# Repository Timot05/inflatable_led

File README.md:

# A portable light printed using Rapid Liquid Printing

## Specs

- 2700K
- About 400 lumens
- Dimmable
- Rechargeable
- Flashes when battery low

## Implementation

- Micro: RP2040
- LED Driver: TPS61165
- LED: OSRAM GW JTLPS1.EM-KKLL-XX58-1
- Batteries: TBD
- Battery charger: TBD

## TODOs for V1 order:

- Check order of LEDs
- Check the caps footprint
- C15, C16 are wrong size
- Remove todo from schematic

## TODOs for v2:

- [x] Add charging status to micro
- [x] fix the led circuit switching
- [x] enable low power mode with reset switch (no long press. How did we switch all circuits on mopi?)
- [x] Remove the cap on qspi_ss
- [x] DNP for the 3.3V led
- [x] Add a buck boost instead of ldo -> Remain with LDO but remove shotky diode (need to add it in case?)
- [x] Check the bat sense feature - probs ok
- [x] White circuit for reflection - will do
- [ ] Add gnd, vref, 3.3V to the debug port
- [x] Add the 10k resistor to the TS pin on the charger -> changed charger and fixed TS
- [x] Switch to ULDO
- [x] Change the battery holder -> changed to double battery holder

Nice to have:

- i2c connected charger
- Protrude the button more
- Nice feeling button

## TODOs for V3

- [ ] add a label for +/- battery
- [ ] remove the pullup on the on/off bt
- [ ] add a blinky led

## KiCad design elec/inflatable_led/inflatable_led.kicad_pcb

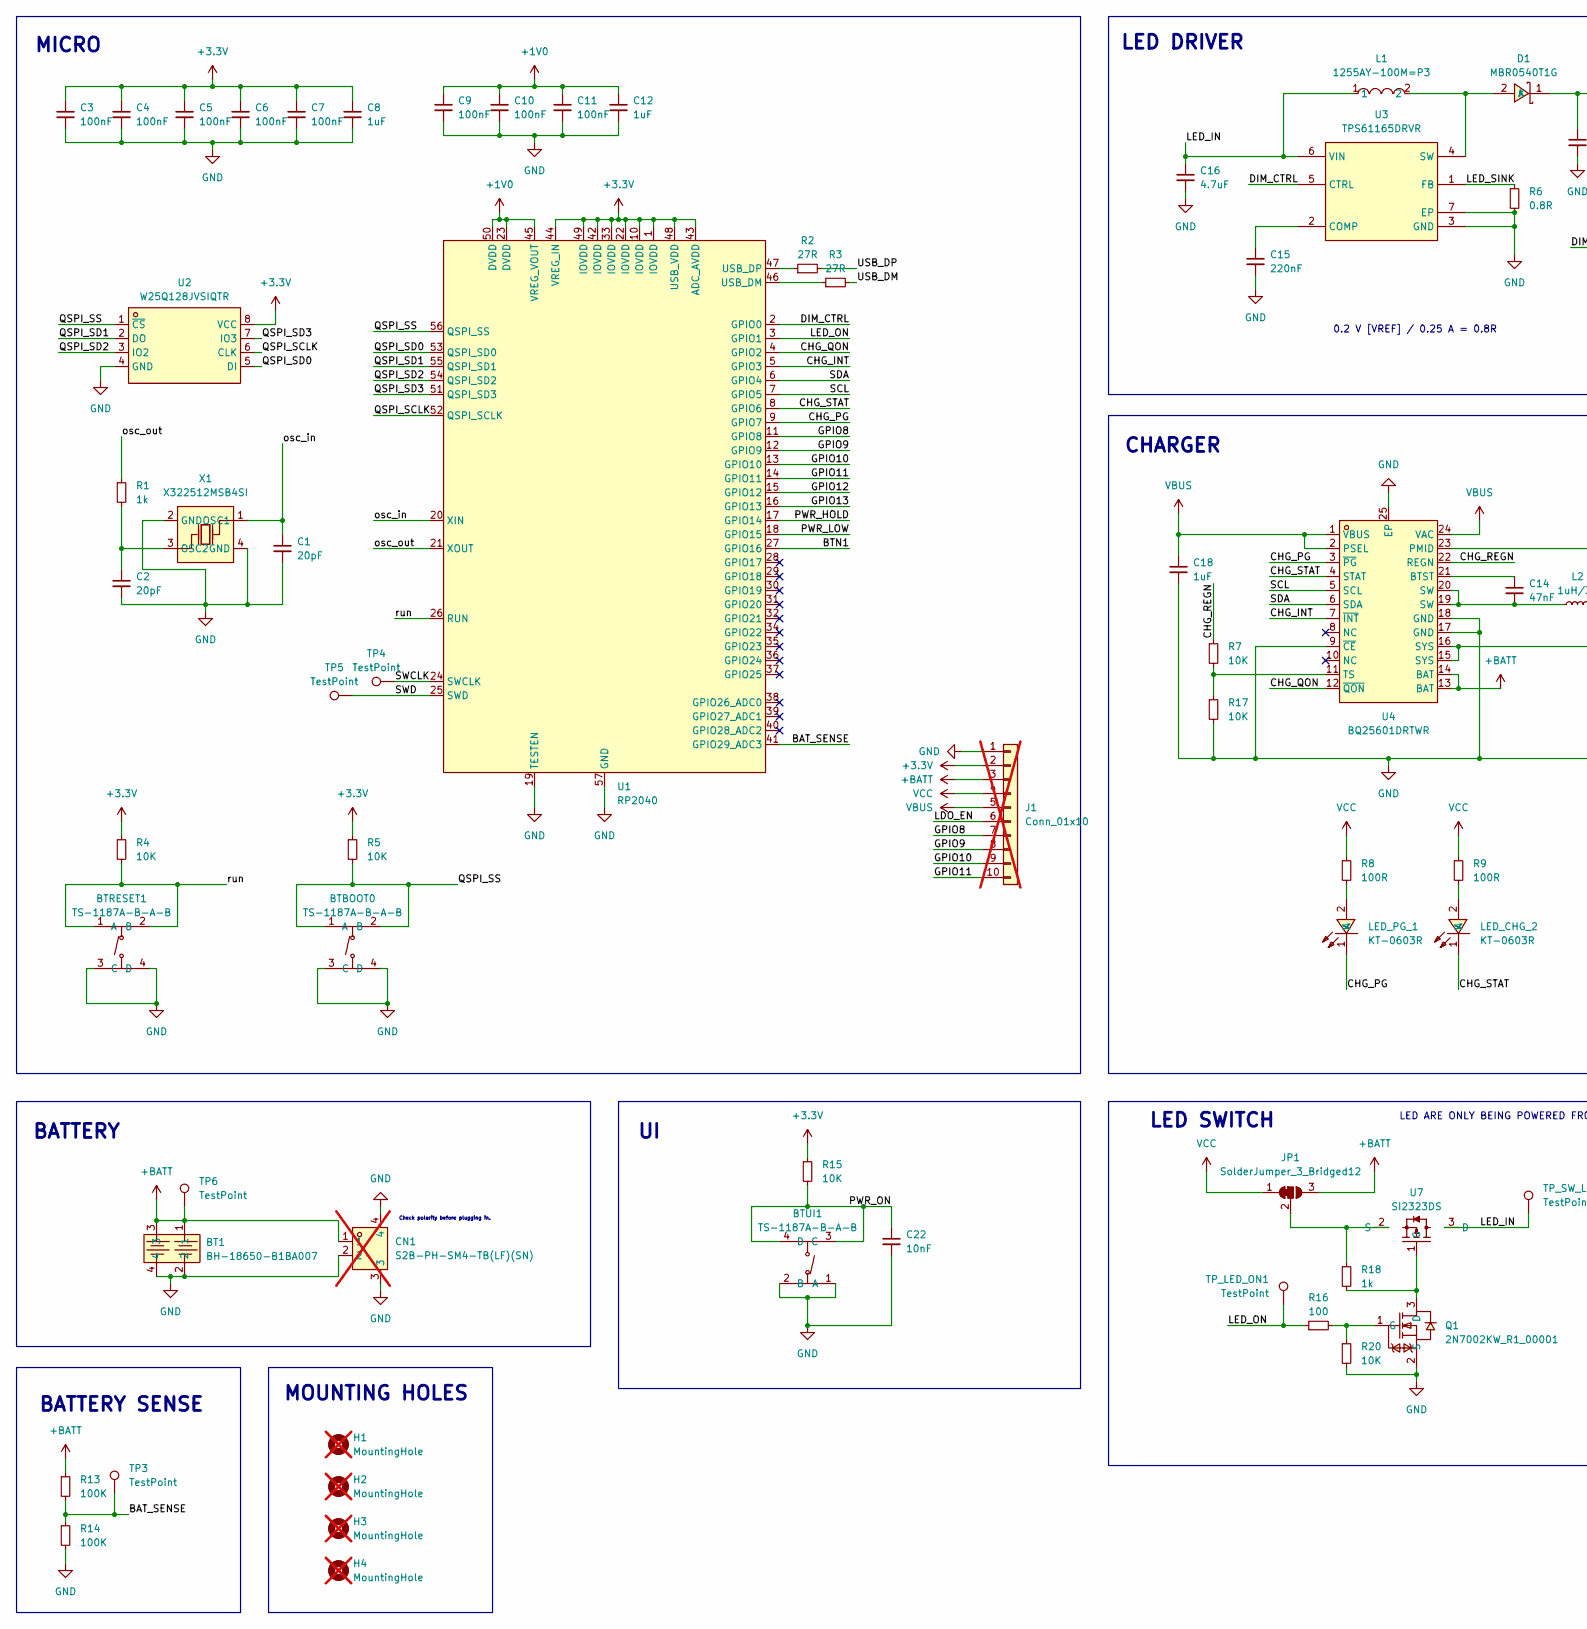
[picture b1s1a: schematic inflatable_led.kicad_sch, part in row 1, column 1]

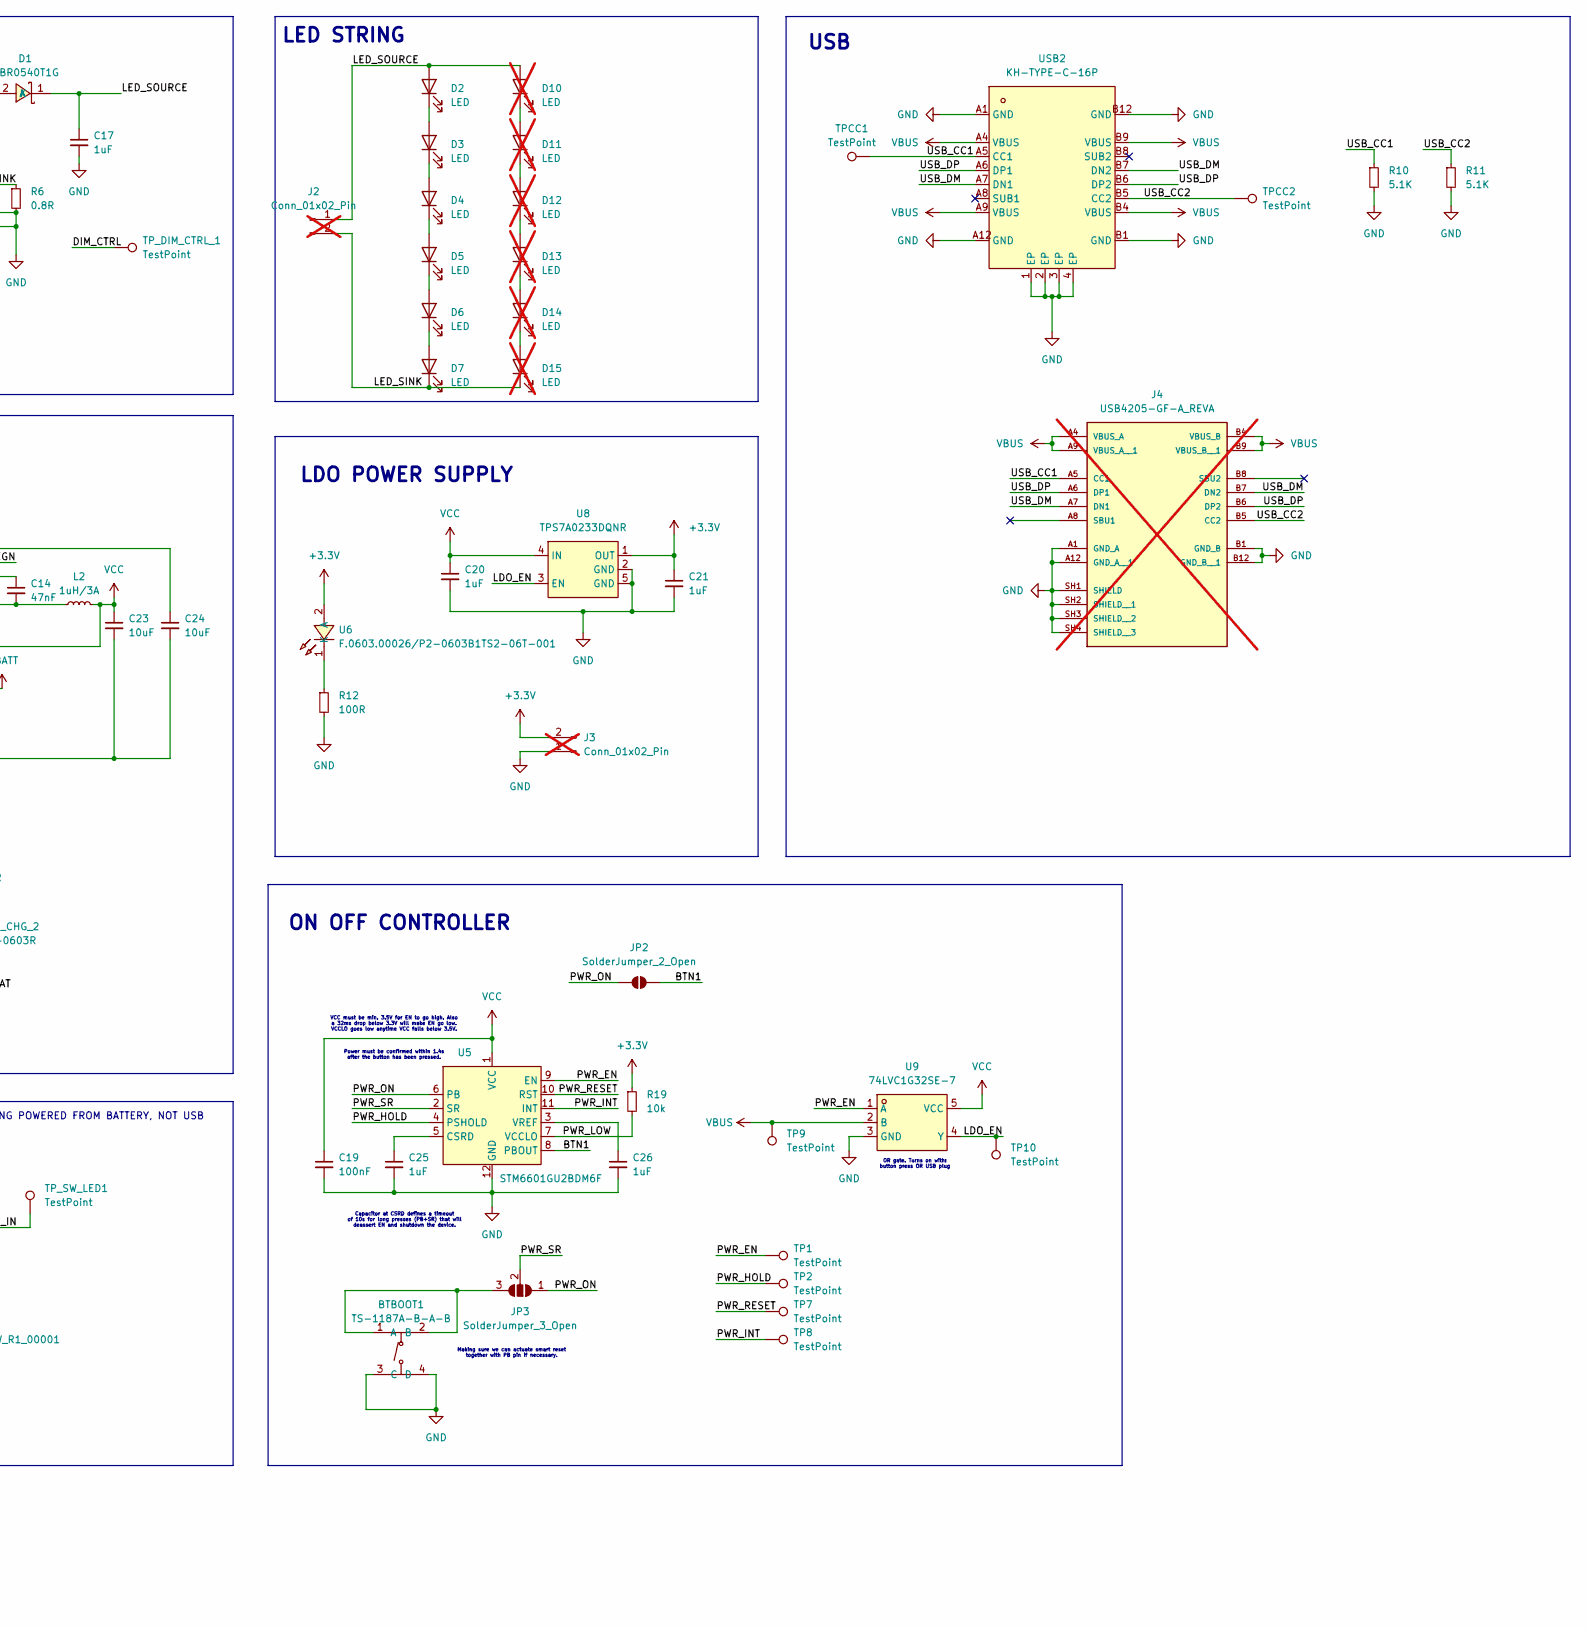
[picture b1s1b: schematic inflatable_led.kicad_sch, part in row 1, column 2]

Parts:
BT1: BH-18650-B1BA007; BAT-SMD_BH-18650-B1BA007; LCSC Part C6937126
BTBOOT0, BTBOOT1: TS-1187A-B-A-B; SW-SMD_4P-L5.1-W5.1-P3.70-LS6.5-TL-2; LCSC Part C318884
BTRESET1: TS-1187A-B-A-B; SW-SMD_4P-L5.1-W5.1-P3.70-LS6.5-TL-2; LCSC Part C318884
BTUI1: TS-1187A-B-A-B; SW-SMD_4P-L5.1-W5.1-P3.70-LS6.5-TL-2; LCSC Part C318884
C1, C2: 20pF; C_0402_1005Metric; LCSC Part C1554
C3, C4, C5, C6, C7, C9, C10, C11: 100nF; C_0402_1005Metric; LCSC Part C1525
C8, C12, C17, C18, C20, C21: 1uF; C_0805_2012Metric; LCSC Part C28323
C14: 47nF; C_0402_1005Metric; Digikey 311-1801-1-ND
C15: 220nF; C_0402_1005Metric; LCSC Part C16772
C16: 4.7uF; C_0402_1005Metric; LCSC Part C23733
C19: 100nF; C_0402_1005Metric; Digikey 311-1776-1-ND
C22: 10nF; C_0402_1005Metric; LCSC Part C15195
C23, C24: 10uF; C_0805_2012Metric; LCSC Part C15850
C25, C26: 1uF; C_0805_2012Metric; Digikey 311-1444-1-ND
CN1: S2B-PH-SM4-TB(LF)(SN); CONN-SMD_P2.00_S2B-PH-SM4-TB-LF-SN; LCSC Part C295747; not fitted
D1: MBR0540T1G; SOD-123_L2.8-W1.8-LS3.7-RD; LCSC Part C109213
D2, D3, D4, D5, D6, D7: LED; GW JTLPS1EM; LCSC Part C5220764
D10: LED; GW JTLPS1EM; LCSC Part C5220764; not fitted
D11, D12, D13, D14, D15: LED; GW JTLPS1EM; not fitted
H1, H2, H3, H4: MountingHole; MountingHole_3.2mm_M3_Pad_Via; not fitted
J1: Conn_01x10; PinHeader_1x10_P1.00mm_Vertical; not fitted
J2, J3: Conn_01x02_Pin; PinHeader_1x02_P2.54mm_Vertical; not fitted
J4: USB4205-GF-A_REVA; GCT_USB4205-GF-A_REVA; PARTREV A; not fitted
JP1: SolderJumper_3_Bridged12; SolderJumper-3_P1.3mm_Bridged12_RoundedPad1.0x1.5mm
JP2: SolderJumper_2_Open; SolderJumper-2_P1.3mm_Open_TrianglePad1.0x1.5mm
JP3: SolderJumper_3_Open; SolderJumper-3_P2.0mm_Open_TrianglePad1.0x1.5mm
L1: 1255AY-100M=P3; IND-SMD_L6.0-W6.0; LCSC Part C160950
L2: 1uH/3A; L_1008_2520Metric; Digikey 1276-6929-1-ND
LED_CHG_2: KT-0603R; LED0603-RD; LCSC Part C2286
LED_PG_1: KT-0603R; LED0603-RD; LCSC Part C2286
Q1: 2N7002KW_R1_00001; SOT-323-3_L2.0-W1.3-P1.30-LS2.1-BR; LCSC Part C313495
R1, R18: 1k; R_0402_1005Metric; LCSC Part C11702
R2, R3: 27R; R_0402_1005Metric; LCSC Part C25100
R4, R5, R7, R15, R17, R20: 10K; R_0402_1005Metric; LCSC Part C25744
R6: 0.8R; R_0805_2012Metric_Pad1.20x1.40mm_HandSolder; LCSC Part C175720
R8, R9, R12: 100R; R_0402_1005Metric; LCSC Part C25076
R10, R11: 5.1K; R_0402_1005Metric; LCSC Part C25905
R13, R14: 100K; R_0402_1005Metric; LCSC Part C25741
R16: 100; R_0402_1005Metric; LCSC Part C25076
R19: 10k; R_0402_1005Metric; Digikey 311-10.0KHRCT-ND
TP1, TP2, TP7, TP8, TP9, TP10: TestPoint; TestPoint_Pad_D1.0mm
TP3, TP4, TP5, TP6: TestPoint; TestPoint_Pad_D1.5mm
TPCC1, TPCC2: TestPoint; TestPoint_Pad_D1.5mm
TP_DIM_CTRL_1: TestPoint; TestPoint_Pad_D1.5mm
TP_LED_ON1: TestPoint; TestPoint_Pad_D1.5mm
TP_SW_LED1: TestPoint; TestPoint_Pad_D1.5mm
U1: RP2040; LQFN-56_L7.0-W7.0-P0.4-EP; LCSC Part C2040
U2: W25Q128JVSIQTR; SOIC-8_L5.3-W5.3-P1.27-LS8.0-BL; LCSC Part C97521
U3: TPS61165DRVR; WSON-6_L2.0-W2.0-P0.65-TL-EP; LCSC Part C122568
U4: BQ25601DRTWR; WQFN-24_L4.0-W4.0-P0.50-TL-EP2.7; LCSC Part C2859691
U5: STM6601GU2BDM6F; TDFN-12_2x3mm_P0.5mm; Digikey 497-14857-1-ND
U6: F.0603.00026/P2-0603B1TS2-06T-001; LED0603-RD; LCSC Part C7496819
U7: SI2323DS; SOT-23-3_L2.9-W1.3-P1.90-LS2.4-BR; LCSC Part C5182044
U8: TPS7A0233DQNR; X2SON-4_L1.0-W1.0-P0.65-TL-EP; LCSC Part C5220177
U9: 74LVC1G32SE-7; SOT-353_L2.0-W1.2-P0.65-LS2.1-BL; LCSC Part C460530
USB2: KH-TYPE-C-16P; USB-C-SMD_KH-TYPE-C-16P; LCSC Part C709357
X1: X322512MSB4SI; OSC-SMD_4P-L3.2-W2.5-BL; LCSC Part C9002

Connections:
+1V0: C9.1, C10.1, C11.1, C12.1, U1.23 (DVDD), U1.45 (VREG_VOUT), U1.50 (DVDD)
+3.3V: C3.1, C4.1, C5.1, C6.1, C7.1, C8.1, C21.1, J1.2, J3.2, R4.1, R5.1, R15.1, R19.1, U1.1 (IOVDD), U1.10 (IOVDD), U1.22 (IOVDD), U1.33 (IOVDD), U1.42 (IOVDD), U1.43 (ADC_AVDD), U1.44 (VREG_IN), U1.48 (USB_VDD), U1.49 (IOVDD), U2.8 (VCC), U6.2 (A), U8.1 (OUT)
+BATT: BT1.1, BT1.3, CN1.1, J1.3, JP1.3 (B), R13.1, TP6.1, U4.13 (BAT), U4.14 (BAT)
/BAT_SENSE: R13.2, R14.1, TP3.1, U1.41 (GPIO29_ADC3)
/BTN1: JP2.2 (B), U1.27 (GPIO16), U5.8 (PBOUT)
/CHG_INT: U1.5 (GPIO3), U4.7 (~INT)
/CHG_PG: LED_PG_1.1 (K), U1.9 (GPIO7), U4.3 (~PG)
/CHG_QON: U1.4 (GPIO2), U4.12 (~QON)
/CHG_REGN: R7.1, U4.22 (REGN)
/CHG_STAT: LED_CHG_2.1 (K), U1.8 (GPIO6), U4.4 (STAT)
/DIM_CTRL: TP_DIM_CTRL_1.1, U1.2 (GPIO0), U3.5 (CTRL)
/GPIO8: J1.7, U1.11 (GPIO8)
/GPIO9: J1.8, U1.12 (GPIO9)
/GPIO10: J1.9, U1.13 (GPIO10)
/GPIO11: J1.10, U1.14 (GPIO11)
/GPIO12: U1.15 (GPIO12)
/GPIO13: U1.16 (GPIO13)
/LDO_EN: J1.6, TP10.1, U8.3 (EN), U9.4 (Y)
/LED_IN: C16.1, L1.1, TP_SW_LED1.1, U3.6 (VIN), U7.3 (D)
/LED_ON: R16.1, TP_LED_ON1.1, U1.3 (GPIO1)
/LED_SINK: D7.1 (K), D15.1 (K), J2.2, R6.1, U3.1 (FB)
/LED_SOURCE: C17.1, D1.1 (K), D2.2 (A), D10.2 (A), J2.1
/PWR_EN: TP1.1, U5.9 (EN), U9.1 (A)
/PWR_HOLD: TP2.1, U1.17 (GPIO14), U5.4 (PSHOLD)
/PWR_INT: TP8.1, U5.11 (INT)
/PWR_LOW: R19.2, U1.18 (GPIO15), U5.7 (VCCLO)
/PWR_ON: BTUI1.3 (C), BTUI1.4 (D), C22.1, JP2.1 (A), JP3.1 (A), R15.2, U5.6 (PB)
/PWR_RESET: TP7.1, U5.10 (RST)
/PWR_SR: JP3.2 (C), U5.2 (SR)
/QSPI_SCLK: U1.52 (QSPI_SCLK), U2.6 (CLK)
/QSPI_SD0: U1.53 (QSPI_SD0), U2.5 (DI)
/QSPI_SD1: U1.55 (QSPI_SD1), U2.2 (DO)
/QSPI_SD2: U1.54 (QSPI_SD2), U2.3 (IO2)
/QSPI_SD3: U1.51 (QSPI_SD3), U2.7 (IO3)
/QSPI_SS: BTBOOT0.1 (A), BTBOOT0.2 (B), R5.2, U1.56 (QSPI_SS), U2.1 (~CS)
/SCL: U1.7 (GPIO5), U4.5 (SCL)
/SDA: U1.6 (GPIO4), U4.6 (SDA)
/SWCLK: TP4.1, U1.24 (SWCLK)
/SWD: TP5.1, U1.25 (SWD)
/USB_CC1: J4.A5 (CC1), R10.1, TPCC1.1, USB2.A5 (CC1)
/USB_CC2: J4.B5 (CC2), R11.1, TPCC2.1, USB2.B5 (CC2)
/USB_DM: J4.A7 (DN1), J4.B7 (DN2), R3.2, USB2.A7 (DN1), USB2.B7 (DN2)
/USB_DP: J4.A6 (DP1), J4.B6 (DP2), R2.2, USB2.A6 (DP1), USB2.B6 (DP2)
/osc_in: C1.1, U1.20 (XIN), X1.1 (OSC1)
/osc_out: R1.1, U1.21 (XOUT)
/run: BTRESET1.1 (A), BTRESET1.2 (B), R4.2, U1.26 (RUN)
GND: BT1.2, BT1.4, BTBOOT0.3 (C), BTBOOT0.4 (D), BTBOOT1.3 (C), BTBOOT1.4 (D), BTRESET1.3 (C), BTRESET1.4 (D), BTUI1.1 (A), BTUI1.2 (B), C1.2, C2.2, C3.2, C4.2, C5.2, C6.2, C7.2, C8.2, C9.2, C10.2, C11.2, C12.2, C15.2, C16.2, C17.2, C18.2, C19.2, C20.2, C21.2, C22.2, C23.2, C24.2, C25.2, C26.2, CN1.2, CN1.3, CN1.4, J1.1, J3.1, J4.A1 (GND_A), J4.A12 (GND_A__1), J4.B1 (GND_B), J4.B12 (GND_B__1), J4.SH1 (SHIELD), J4.SH2 (SHIELD__1), J4.SH3 (SHIELD__2), J4.SH4 (SHIELD__3), Q1.2 (S), R6.2, R10.2, R11.2, R12.2, R14.2, R17.2, R20.2, U1.19 (TESTEN), U1.57 (GND), U2.4 (GND), U3.3 (GND), U3.7 (EP), U4.9 (~CE), U4.17 (GND), U4.18 (GND), U4.25 (EP), U5.12 (GND), U8.2 (GND), U8.5 (GND), U9.3 (GND), USB2.1 (EP), USB2.2 (EP), USB2.3 (EP), USB2.4 (EP), USB2.A1 (GND), USB2.A12 (GND), USB2.B1 (GND), USB2.B12 (GND), X1.2 (GND), X1.4 (GND)
unnamed: BTBOOT1.1 (A), BTBOOT1.2 (B), JP3.3 (B)
unnamed: C14.2, L2.1, U4.19 (SW), U4.20 (SW)
unnamed: D1.2 (A), L1.2, U3.4 (SW)
unnamed: D2.1 (K), D3.2 (A)
unnamed: D3.1 (K), D4.2 (A)
unnamed: D4.1 (K), D5.2 (A)
unnamed: D5.1 (K), D6.2 (A)
unnamed: D6.1 (K), D7.2 (A)
unnamed: D10.1 (K), D11.2 (A)
unnamed: D11.1 (K), D12.2 (A)
unnamed: D12.1 (K), D13.2 (A)
unnamed: D13.1 (K), D14.2 (A)
unnamed: D14.1 (K), D15.2 (A)
unnamed: JP1.2 (C), R18.1, U7.2 (S)
unnamed: LED_CHG_2.2 (A), R9.2
unnamed: LED_PG_1.2 (A), R8.2
unnamed: Q1.3 (D), R18.2, U7.1 (G)
unnamed: Q1.1 (G), R16.2, R20.1
unnamed: R3.1, U1.46 (USB_DM)
unnamed: R2.1, U1.47 (USB_DP)
unnamed: C15.1, U3.2 (COMP)
unnamed: C14.1, U4.21 (BTST)
unnamed: C24.1, U4.23 (PMID)
unnamed: R7.2, R17.1, U4.11 (TS)
unnamed: C25.1, U5.5 (CSRD)
unnamed: C26.1, U5.3 (VREF)
unnamed: R12.1, U6.1 (K)
unnamed: C2.1, R1.2, X1.3 (OSC2)
VBUS: C18.1, J1.5, J4.A4 (VBUS_A), J4.A9 (VBUS_A__1), J4.B4 (VBUS_B), J4.B9 (VBUS_B__1), TP9.1, U4.1 (VBUS), U4.2 (PSEL), U4.24 (VAC), U9.2 (B), USB2.A4 (VBUS), USB2.A9 (VBUS), USB2.B4 (VBUS), USB2.B9 (VBUS)
VCC: C19.1, C20.1, C23.1, J1.4, JP1.1 (A), L2.2, R8.1, R9.1, U4.15 (SYS), U4.16 (SYS), U5.1 (VCC), U8.4 (IN), U9.5 (VCC)

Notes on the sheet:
OR gate. Turns on with: button press OR USB plug
VCC must be min. 3.5V for EN to go high. Also a 32ms drop below 3.3V will make EN go low. VCCLO goes low anytime VCC falls below 3.5V. Power must be confirmed within 1.4s after the button has been pressed.
Capacitor at CSRD defines a timeout of 10s for long presses (PB+SR) that will deassert EN and shutdown the device.
LED ARE ONLY BEING POWERED FROM BATTERY, NOT USB
Check polarity before plugging in.
Making sure we can actuate smart reset together with PB pin if necessary.
BATTERY
0.2 V [VREF] / 0.25 A = 0.8R
LED SWITCH
LED STRING
MOUNTING HOLES
ON OFF CONTROLLER
CHARGER
LDO POWER SUPPLY
LED DRIVER
USB
BATTERY SENSE
MICRO

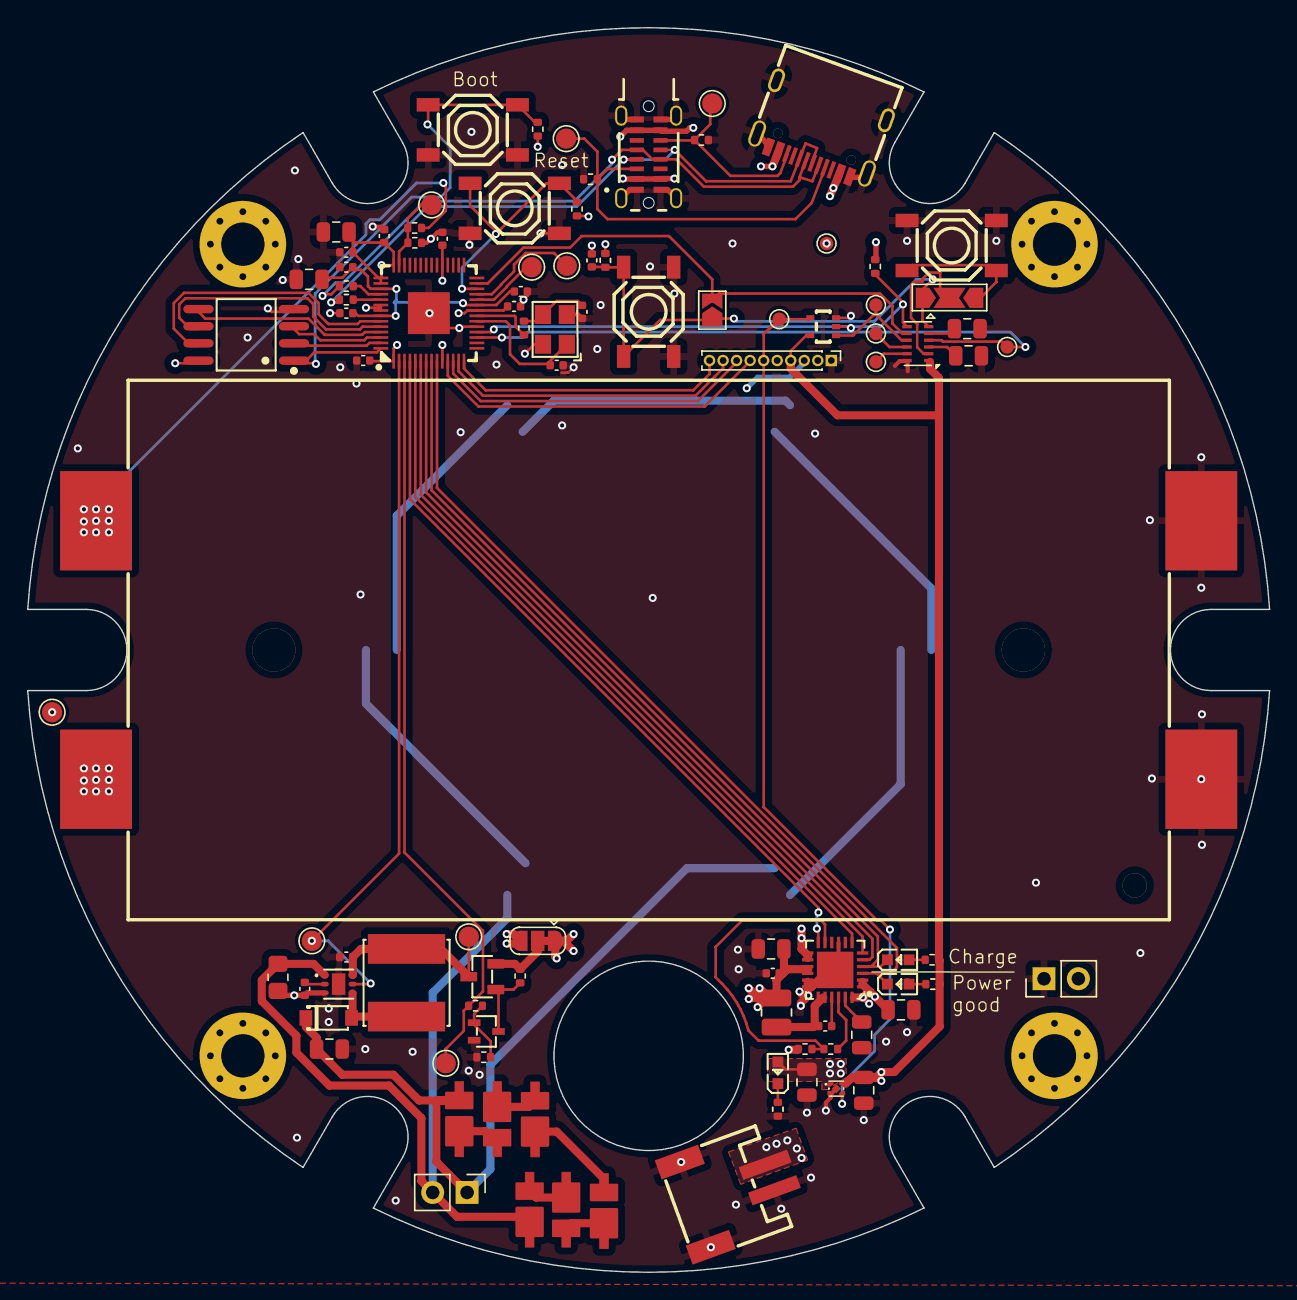
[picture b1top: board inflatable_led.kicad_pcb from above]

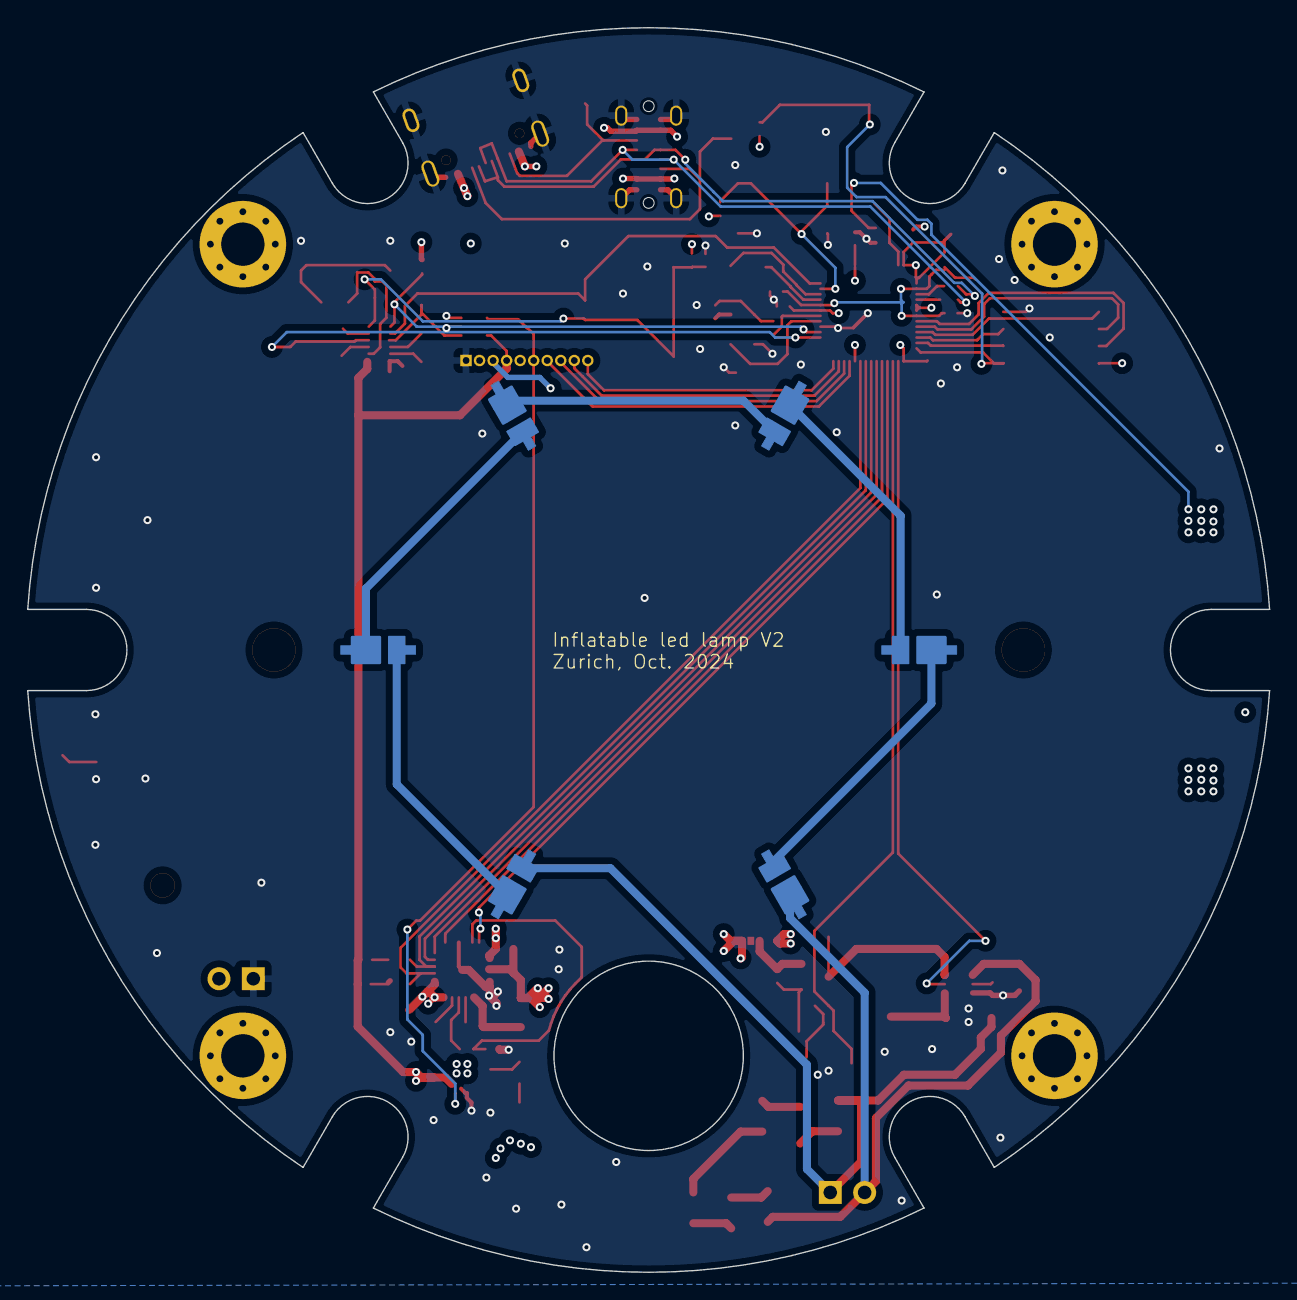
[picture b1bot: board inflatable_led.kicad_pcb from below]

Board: 4 copper layers, 91.8 x 92.0 mm, 106 parts (6 on the bottom side), 75 nets.

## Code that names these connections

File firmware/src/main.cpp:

#include <Arduino.h>
#include "main.h"

#include "pico/stdlib.h"
#include "hardware/pwm.h"

#include "../lib/StateMachine/StateMachine.hpp"
#include "../lib/StateMachine/State.hpp"

#include "../lib/bq25601/bq25601.h"

#define PRINT_DEBUG 0

unsigned long lastPressTime = 0;      // Last time the button was pressed

const unsigned long shortPressDuration = 1000;

StateMachine state_machine;
State state;

unsigned int brightness = 1;

uint slice_num;

void handleButtonPress() {
    lastPressTime = millis();
}

void handleButtonRelease() {
    unsigned long currentTime = millis();
    unsigned long pressDuration = currentTime - lastPressTime;

    if (2 < pressDuration < shortPressDuration) {
        state_machine.shortPress();
    }
}

void handleButtonChange() {
    if (digitalRead(BTN_1_PIN) == LOW) {
        handleButtonPress();
    } else {
        handleButtonRelease();
    }
}

// int is active low
bool chr_int = false;
void handleChgInt() {
    chr_int = true;
}


void setup() {
    #if PRINT_DEBUG
    Serial1.begin(115200); // USB serial
    Serial2.setTX(8); // Set TX to GPIO10
    Serial2.setRX(9); // Set RX to GPIO11
    Serial2.begin(115200); // UART serial
    #endif

    pinMode(CHG_STAT_PIN, INPUT);
    pinMode(CHG_PG_PIN, INPUT);
    pinMode(CHG_INT_PIN, INPUT_PULLUP);
    attachInterrupt(digitalPinToInterrupt(CHG_INT_PIN), handleChgInt, FALLING);
    pinMode(CHG_SDA_PIN, INPUT_PULLUP);
    pinMode(CHG_SCL_PIN, INPUT_PULLUP);

    pinMode(CHG_QON_PIN, OUTPUT);
    digitalWrite(CHG_QON_PIN, HIGH);

    // Setup the led pins
    pinMode(LED_ON_PIN, OUTPUT);
    pinMode(LED_DIM_CTRL_PIN, OUTPUT);

    pinMode(BTN_1_PIN, INPUT_PULLUP);

    // delay(20);
    // Power hold at startup
    pinMode(PWR_HOLD, OUTPUT);
    digitalWrite(PWR_HOLD, HIGH);

    attachInterrupt(digitalPinToInterrupt(BTN_1_PIN), handleButtonChange, CHANGE);

    digitalWrite(LED_ON_PIN, HIGH);

    gpio_set_function(LED_DIM_CTRL_PIN, GPIO_FUNC_PWM);
    slice_num = pwm_gpio_to_slice_num(LED_DIM_CTRL_PIN);
    pwm_set_wrap(slice_num, 12499);


    if(!bq25601_init()) {
        #if PRINT_DEBUG
        Serial.println("Charger init failed!");
        #endif
        bq25601_writeRegister(REG00, 0b00010111);
    }
}

#define BR_1 1
#define BR_2 50
#define BR_3 255

void loop() {
    unsigned long currentTime = millis();

    state = state_machine.getState();

    #if PRINT_DEBUG
    void debugPrint(const char* stateName) {
        Serial.println(stateName);
        Serial2.println(stateName);
    }
    #endif

    switch (state) {
        case State::OFF:
            #if PRINT_DEBUG
            debugPrint("OFF");
            #endif
            digitalWrite(PWR_HOLD, LOW);
            break;

        case State::ON_1:
        case State::ON_2:
        case State::ON_3: {
            #if PRINT_DEBUG
            if (state == State::ON_1) debugPrint("ON_1");
            else if (state == State::ON_2) debugPrint("ON_2");
            else debugPrint("ON_3");
            #endif

            uint8_t brightness = (state == State::ON_1) ? BR_1 :
                                (state == State::ON_2) ? BR_2 : BR_3;

            unsigned int value = map(brightness, 0, 255, 0, 12499);
            pwm_set_chan_level(slice_num, PWM_CHAN_A, value);
            pwm_set_enabled(slice_num, true);
            break;
        }

        case State::CHARGING:
            #if PRINT_DEBUG
            debugPrint("CHARGING");
            #endif
            digitalWrite(PWR_HOLD, LOW);
            digitalWrite(LED_ON_PIN, LOW);
            break;

        default:
            #if PRINT_DEBUG
            debugPrint("UNKNOWN");
            #endif
            break;
    }

    if (digitalRead(BTN_1_PIN) == LOW && shortPressDuration < currentTime - lastPressTime) {
        state_machine.longPress();
    }

    // Handle charger states
    // if (chr_int) {
    //     Serial2.println("Charger interrupt");
    //     Serial2.print("Previous message: ");
    //     Serial2.println(bq25601_readRegister(REG09), BIN);
    //     Serial2.print("Current message: ");
    //     Serial2.println(bq25601_readRegister(REG09), BIN);
    //     chr_int = false;
    // }

    // Serial2.println("Charger interrupt");
    // Serial2.print("Previous message: ");
    // Serial2.println(bq25601_readRegister(REG02), BIN);
    // Serial2.print("Current message: ");
    // Serial2.println(bq25601_readRegister(REG02), BIN);

    bq2501_updateStatus();
    if (bq2501_get_vbus() != NO_INPUT) {
        if (bq2501_get_chrg() == PRE_CHARGE1 || bq2501_get_chrg() == FAST_CHARGE) {
            state_machine.charging();
        }
        else if (bq2501_get_chrg() == CHARGE_DONE) {
            state_machine.charged();
        }
        else {
            state_machine.error();
        }
    }
    else {
        state_machine.not_plugged();
    }

    delay(50);
}

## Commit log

2024-08-22 add micro
2024-09-01 progress on schematic
2024-09-05 checking schematic
2024-09-11 layout almost done + CI
2024-09-11 fix ci
2024-09-11 add specific config file
2024-09-11 fix all unconnected items
2024-09-11 change ERC error level
2024-09-11 change layout
2024-09-11 change CI
2024-09-11 add 3D files
2024-09-11 add all part numbers
2024-09-11 add ci step
2024-09-11 fix cpl file
2024-09-11 exclude from pos file
2024-09-12 fix footprint + add pn
2024-09-12 fix more footprints
2024-09-12 leds in the wrong order
2024-09-12 add updated enclosure
2024-09-26 fix missing 3.3V on flash
2024-09-28 v1 is working, add v2 requests
2024-09-28 minor schematic changes
2024-09-29 fix lower light limit
2024-10-14 whole new circuit
2024-10-14 update bom
2024-10-14 fix additional parts in BOM
2024-10-14 final tweaks
2024-10-15 dnp battery conn
2024-10-15 add a few silkscreen items
2024-10-15 add OR gate to circuit
2024-12-15 project is working
